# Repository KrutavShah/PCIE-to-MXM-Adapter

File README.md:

# PCIE to MXM Adapter
This adapter/card allows you to plug an MXM 3.0/3.1 graphics card into a desktop PCI Express port.
There's multiple use cases for this, including MXM card testing, repair, basic computer use, gaming, light workstation use, and more.
This adapter design has been made publicly viewable for educational purposes. 
I made this desicion because of the very high prices that these MXM adapters usually go for online, 
as well as to allow the general public to understand how MXM cards can be interfaced 
with computers to function.
As always, feel free to create issues on this repository and contribute to the project.

## Current Progress

**Early Prototype:**

What Works:

- HDMI port can output, only version 1.4 bandwidths were tested.
- PCI-e Gen 2 link speed.
- MXM Type-A card fully functional on PCI-e x1 slot power.
- Boot screen and BIOS are accessible through it.
- Can play games and use workstation software.

What Might Not Work:

- PWM fan speed, this feature is dependent on the MXM card's manufacturer including support for it.
- HDMI may show up as a DVI port on some combination of cards and monitors. Further testing will be necessary.

Other features have not been tested due to a lack of MXM cards to test with, such as HDMI Version 2.0 bandwidth. I only have one card, the AMD FirePro M4000, which is an old card and not the best candidate for testing.

**Note:** this is the first prototype and much has changed since it was produced.

## Licensing information
The work of this project is property of Krutav Shah, &copy; 2022. 
Reproduction is not allowed. Commercial use is prohibited.

Some of the material here, such as the footprints in the parts library are the works of various providers such as Molex LLC. Those organizations hold the rights to those resources that have been used in this project.

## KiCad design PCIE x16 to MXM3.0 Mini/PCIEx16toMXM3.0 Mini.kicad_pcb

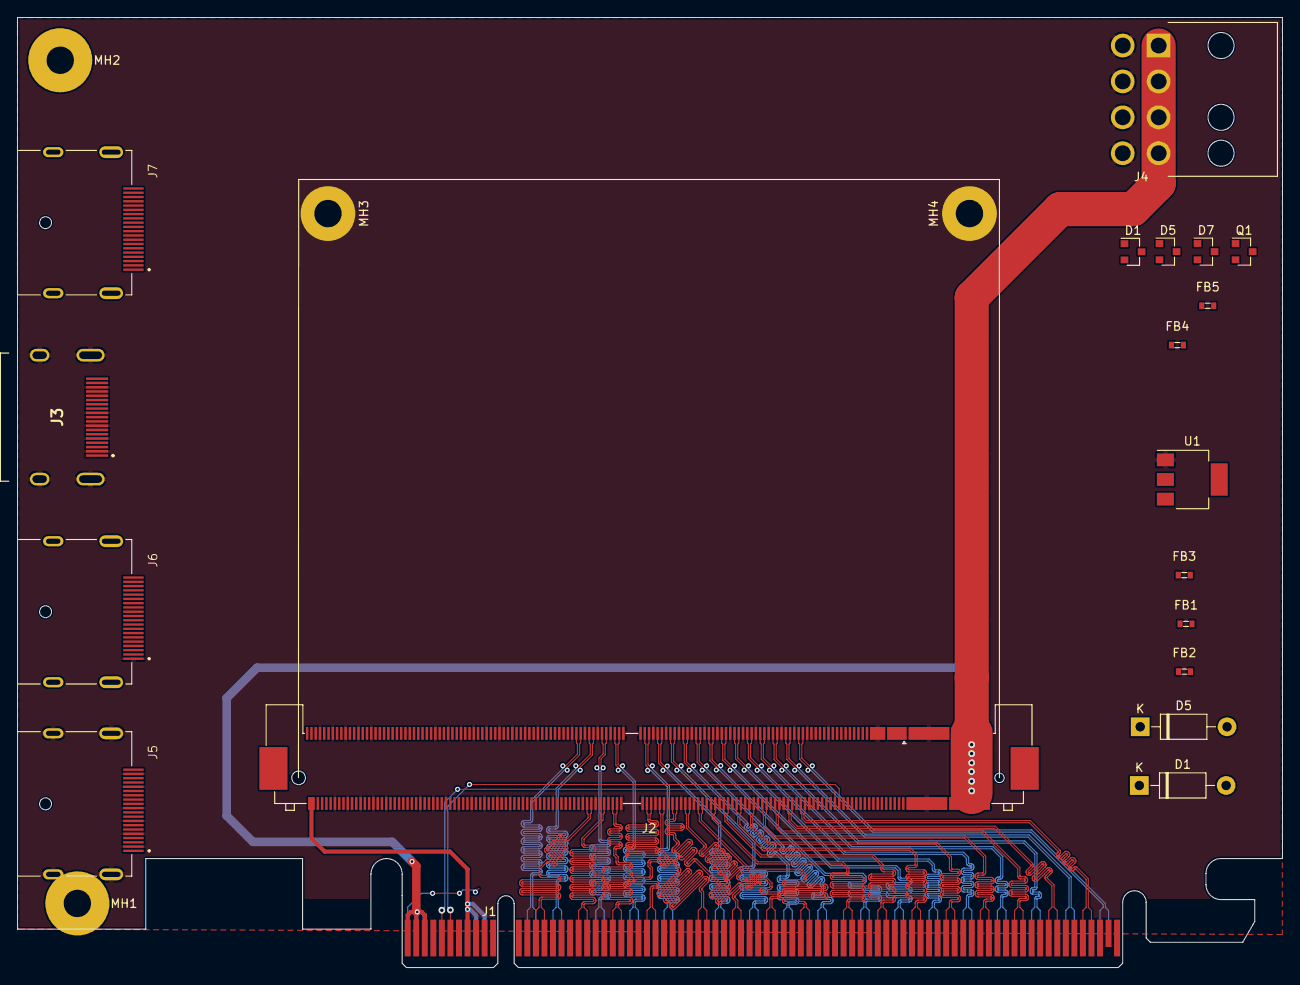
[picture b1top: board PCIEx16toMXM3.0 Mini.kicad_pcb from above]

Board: 4 copper layers, 148.0 x 111.2 mm, 23 parts (0 on the bottom side), 102 nets.

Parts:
D1, D5: PMEG4010ET; D_DO-41_SOD81_P10.16mm_Horizontal
D1#2, D5#2, D7: PMEG4010ET; D_SOT-23_ANK
FB1, FB2, FB3, FB4, FB5: BLM18PG121SN1D; 0603
J1: Bus_PCI_Express_x16; BUS_PCIexpress_x16
J2: MXM3.0; JAE_MM70-314-310B1
J3: 208658-1081; 2086581081
J4: Molex-45586 8 Pin PWR; Molex_45586-8-Pin-PWR
J5: 47272-0001; MOLEX_47272-0001
J6: Fan_4pin; MOLEX_47272-0001
J7: MOLEX_47272-0001
MH1, MH2, MH3, MH4: MountingHole_3.2mm_M3_Pad
Q1: BC848; SOT-23
U1: AMS1117-5.0; SOT-223-3_TabPin2

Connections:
+3.3VA: J1.B10, Q1.3
+3V3: J1.A9, J1.A10, J1.B8, J2.278, J2.280, J5.20
+5V: J2.1, J2.3, J2.5, J2.7, J2.9, J3.18
+12V: D1.2, D1#2.2, D7.2, J1.A2, J1.A3, J1.B1, J1.B2, J1.B3, J2.E1, J2.E2, J4.1, J4.2, J4.3, J4.4
/CK_N: J2.176, J3.12
/CK_P: J2.178, J3.10
/CLKREQ#: J1.B12, J2.154
/D0_N: J2.200, J3.9
/D0_P: J2.202, J3.7
/D1_N: J2.194, J3.6
/D1_P: J2.196, J3.4
/D2_N: J2.188, J3.3
/D2_P: J2.190, J3.1
/DP_A_HPD: J2.273, J2.276, J5.18
/DP_C_HPD: J2.234, J2.274
/PER0_N: J1.A17, J2.147
/PER0_P: J1.A16, J2.149
/PER1_N: J1.A22, J2.141
/PER1_P: J1.A21, J2.143
/PER2_N: J1.A26, J2.135
/PER2_P: J1.A25, J2.137
/PER3_N: J1.A30, J2.121
/PER3_P: J1.A29, J2.123
/PER4_N: J1.A36, J2.115
/PER4_P: J1.A35, J2.117
/PER5_N: J1.A40, J2.109
/PER5_P: J1.A39, J2.111
/PER6_N: J1.A44, J2.103
/PER6_P: J1.A43, J2.105
/PER7_N: J1.A48, J2.97
/PER7_P: J1.A47, J2.99
/PER8_N: J1.A53, J2.91
/PER8_P: J1.A52, J2.93
/PER9_N: J1.A57, J2.85
/PER9_P: J1.A56, J2.87
/PER10_N: J1.A61, J2.79
/PER10_P: J1.A60, J2.81
/PER11_N: J1.A65, J2.73
/PER11_P: J1.A64, J2.75
/PER12_N: J1.A69, J2.67
/PER12_P: J1.A68, J2.69
/PER13_N: J1.A73, J2.61
/PER13_P: J1.A72, J2.63
/PER14_N: J1.A77, J2.55
/PER14_P: J1.A76, J2.57
/PER15_N: J1.A81, J2.49
/PER15_P: J1.A80, J2.51
/PERST: J1.A11, J2.156, Q1.2
/PET0_N: J1.B15, J2.148
/PET0_P: J1.B14, J2.150
/PET1_N: J1.B20, J2.142
/PET1_P: J1.B19, J2.144
/PET2_N: J1.B24, J2.136
/PET2_P: J1.B23, J2.138
/PET3_N: J1.B28, J2.120
/PET3_P: J1.B27, J2.122
/PET4_N: J1.B34, J2.114
/PET4_P: J1.B33, J2.116
/PET5_N: J1.B38, J2.108
/PET5_P: J1.B37, J2.110
/PET6_N: J1.B42, J2.102
/PET6_P: J1.B41, J2.104
/PET7_N: J1.B46, J2.96
/PET7_P: J1.B45, J2.98
/PET8_N: J1.B51, J2.90
/PET8_P: J1.B50, J2.92
/PET9_N: J1.B55, J2.84
/PET9_P: J1.B54, J2.86
/PET10_N: J1.B59, J2.78
/PET10_P: J1.B58, J2.80
/PET11_N: J1.B63, J2.72
/PET11_P: J1.B62, J2.74
/PET12_N: J1.B67, J2.66
/PET12_P: J1.B66, J2.68
/PET13_N: J1.B71, J2.60
/PET13_P: J1.B70, J2.62
/PET14_N: J1.B75, J2.54
/PET14_P: J1.B74, J2.56
/PET15_N: J1.B79, J2.48
/PET15_P: J1.B78, J2.50
/REFCLK_N: J1.A14, J2.153
/REFCLK_P: J1.A13, J2.155
/SMCLK: J1.B5, J2.34
/SMDAT: J1.B6, J2.32
/TH_OVERT#: J2.20, Q1.1
/TMDS_HPD: J2.31, J3.19
/TMDS_SCL: J2.35, J3.15
/TMDS_SDA: J2.33, J3.16
/WAKE: J1.B11, J2.4
CEC: J2.29, J3.13
GND: J1.A4, J1.A12, J1.A15, J1.A18, J1.A20, J1.A23, J1.A24, J1.A27, J1.A28, J1.A31, J1.A34, J1.A37, J1.A38, J1.A41, J1.A42, J1.A45, J1.A46, J1.A49, J1.A51, J1.A54, J1.A55, J1.A58, J1.A59, J1.A62, J1.A63, J1.A66, J1.A67, J1.A70, J1.A71, J1.A74, J1.A75, J1.A78, J1.A79, J1.A82, J1.B4, J1.B7, J1.B13, J1.B16, J1.B18, J1.B21, J1.B22, J1.B25, J1.B26, J1.B29, J1.B32, J1.B35, J1.B36, J1.B39, J1.B40, J1.B43, J1.B44, J1.B47, J1.B49, J1.B52, J1.B53, J1.B56, J1.B57, J1.B60, J1.B61, J1.B64, J1.B65, J1.B68, J1.B69, J1.B72, J1.B73, J1.B76, J1.B77, J1.B80, J2.11, J2.13, J2.15, J2.17, J2.36, J2.37, J2.46, J2.47, J2.52, J2.53, J2.58, J2.59, J2.64, J2.65, J2.70, J2.71, J2.76, J2.77, J2.82, J2.83, J2.88, J2.89, J2.94, J2.95, J2.100, J2.101, J2.106, J2.107, J2.112, J2.113, J2.118, J2.119, J2.124, J2.125, J2.133, J2.134, J2.139, J2.140, J2.145, J2.146, J2.151, J2.152, J2.157, J2.166, J2.173, J2.174, J2.179, J2.180, J2.185, J2.186, J2.191, J2.192, J2.197, J2.198, J2.203, J2.204, J2.209, J2.210, J2.215, J2.216, J2.221, J2.222, J2.228, J2.244, J2.250, J2.251, J2.256, J2.257, J2.262, J2.263, J2.268, J2.269, J2.275, J2.E3, J2.E4, J3.2, J3.5, J3.8, J3.11, J3.17, J3.MH1, J3.MH2, J3.MH3, J3.MH4, J4.5, J4.6, J4.7, J4.8, J5.2, J5.5, J5.8, J5.11, J5.16, J5.19, J5.S1, J5.S2, J5.S3, J5.S4, J6.1, MH3.1, MH4.1, U1.1
unnamed: D1.1, D1#2.1, U1.3
unnamed: D5.1, D5#2.1
unnamed: D5.2, D5#2.2, U1.2
unnamed: D7.1, J6.2
unnamed: FB1.1, J2.164
unnamed: FB2.1, J2.162
unnamed: FB3.1, J2.172
unnamed: FB4.1, J2.170
unnamed: FB5.2, J2.168
unnamed: J1.A1, J1.B17, J1.B31, J1.B48, J1.B81
TH_PWM: J2.24, J6.4

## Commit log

2021-02-22 Added initial build version 1.0
2021-02-22 Rename README.txt to README.md
2021-02-23 Fixed minor issues
2021-02-23 Added LICENSE
2021-02-23 Reupload Files
2021-02-23 Updated gitignore
2021-02-23 Added README for x1 adapter
2021-02-23 Update README for x1 adapter
2021-02-27 Updated Licensing
2021-02-27 Added x16 base files
2021-03-03 Added x16 prototype
2021-03-03 Started work on x16 adapter
2021-03-04 Made progress on PCIE x16 adapter
2021-03-06 Updated parts
2021-03-08 Made some changes
2021-03-30 Made some changes and added new Altium documents
2021-04-23 Began transition to Altium.
2021-04-24 Basic dimensions of the x1 adapter made.
2021-04-24 Updated .gitignore
2021-04-25 Worked on the designs.
2021-04-26 Done some work on the adapters.
2021-04-26 Fixed 3.3V pin.
2021-04-27 Add 5V rail and other improvements.
2021-04-28 Made a few improvements.
2021-04-29 Updated .gitignore.
2021-04-29 Attempted another fix for the repository.
2021-04-29 Attempting fix 2 for the repository.
2021-05-12 Uploading progress with unresolved errors.
2021-05-31 Completed most circuits and switched to 4 layer PCB.
2021-05-31 Added render of updated PCB.
2021-05-31 Updated README to include new photo.
2021-06-13 Updated +5V and improved some aspects of the design.
2021-06-17 Reduced via count, improved +5V rail, and other parts of the design.
2021-06-20 Fixed some design rules and copper pours.
2021-07-07 Added testpoints, working towards finalizing PCB design.
2021-08-01 Made minor improvements, enlarged some testpoints.
2021-08-23 Improved overall layout and reworked power delivery.
2021-11-07 Cleaned up layout more, added +12V protection circuit to schematics.
2021-11-07 Added new images of the project.
2021-11-07 Update README to show new render of project.
2022-01-23 Made improvements to power delivery, added current limiter.
2022-01-24 Added bypass capacitors, cleaned up schematics.
2022-09-19 Uploaded prototype info and pending changes of the adapter.
